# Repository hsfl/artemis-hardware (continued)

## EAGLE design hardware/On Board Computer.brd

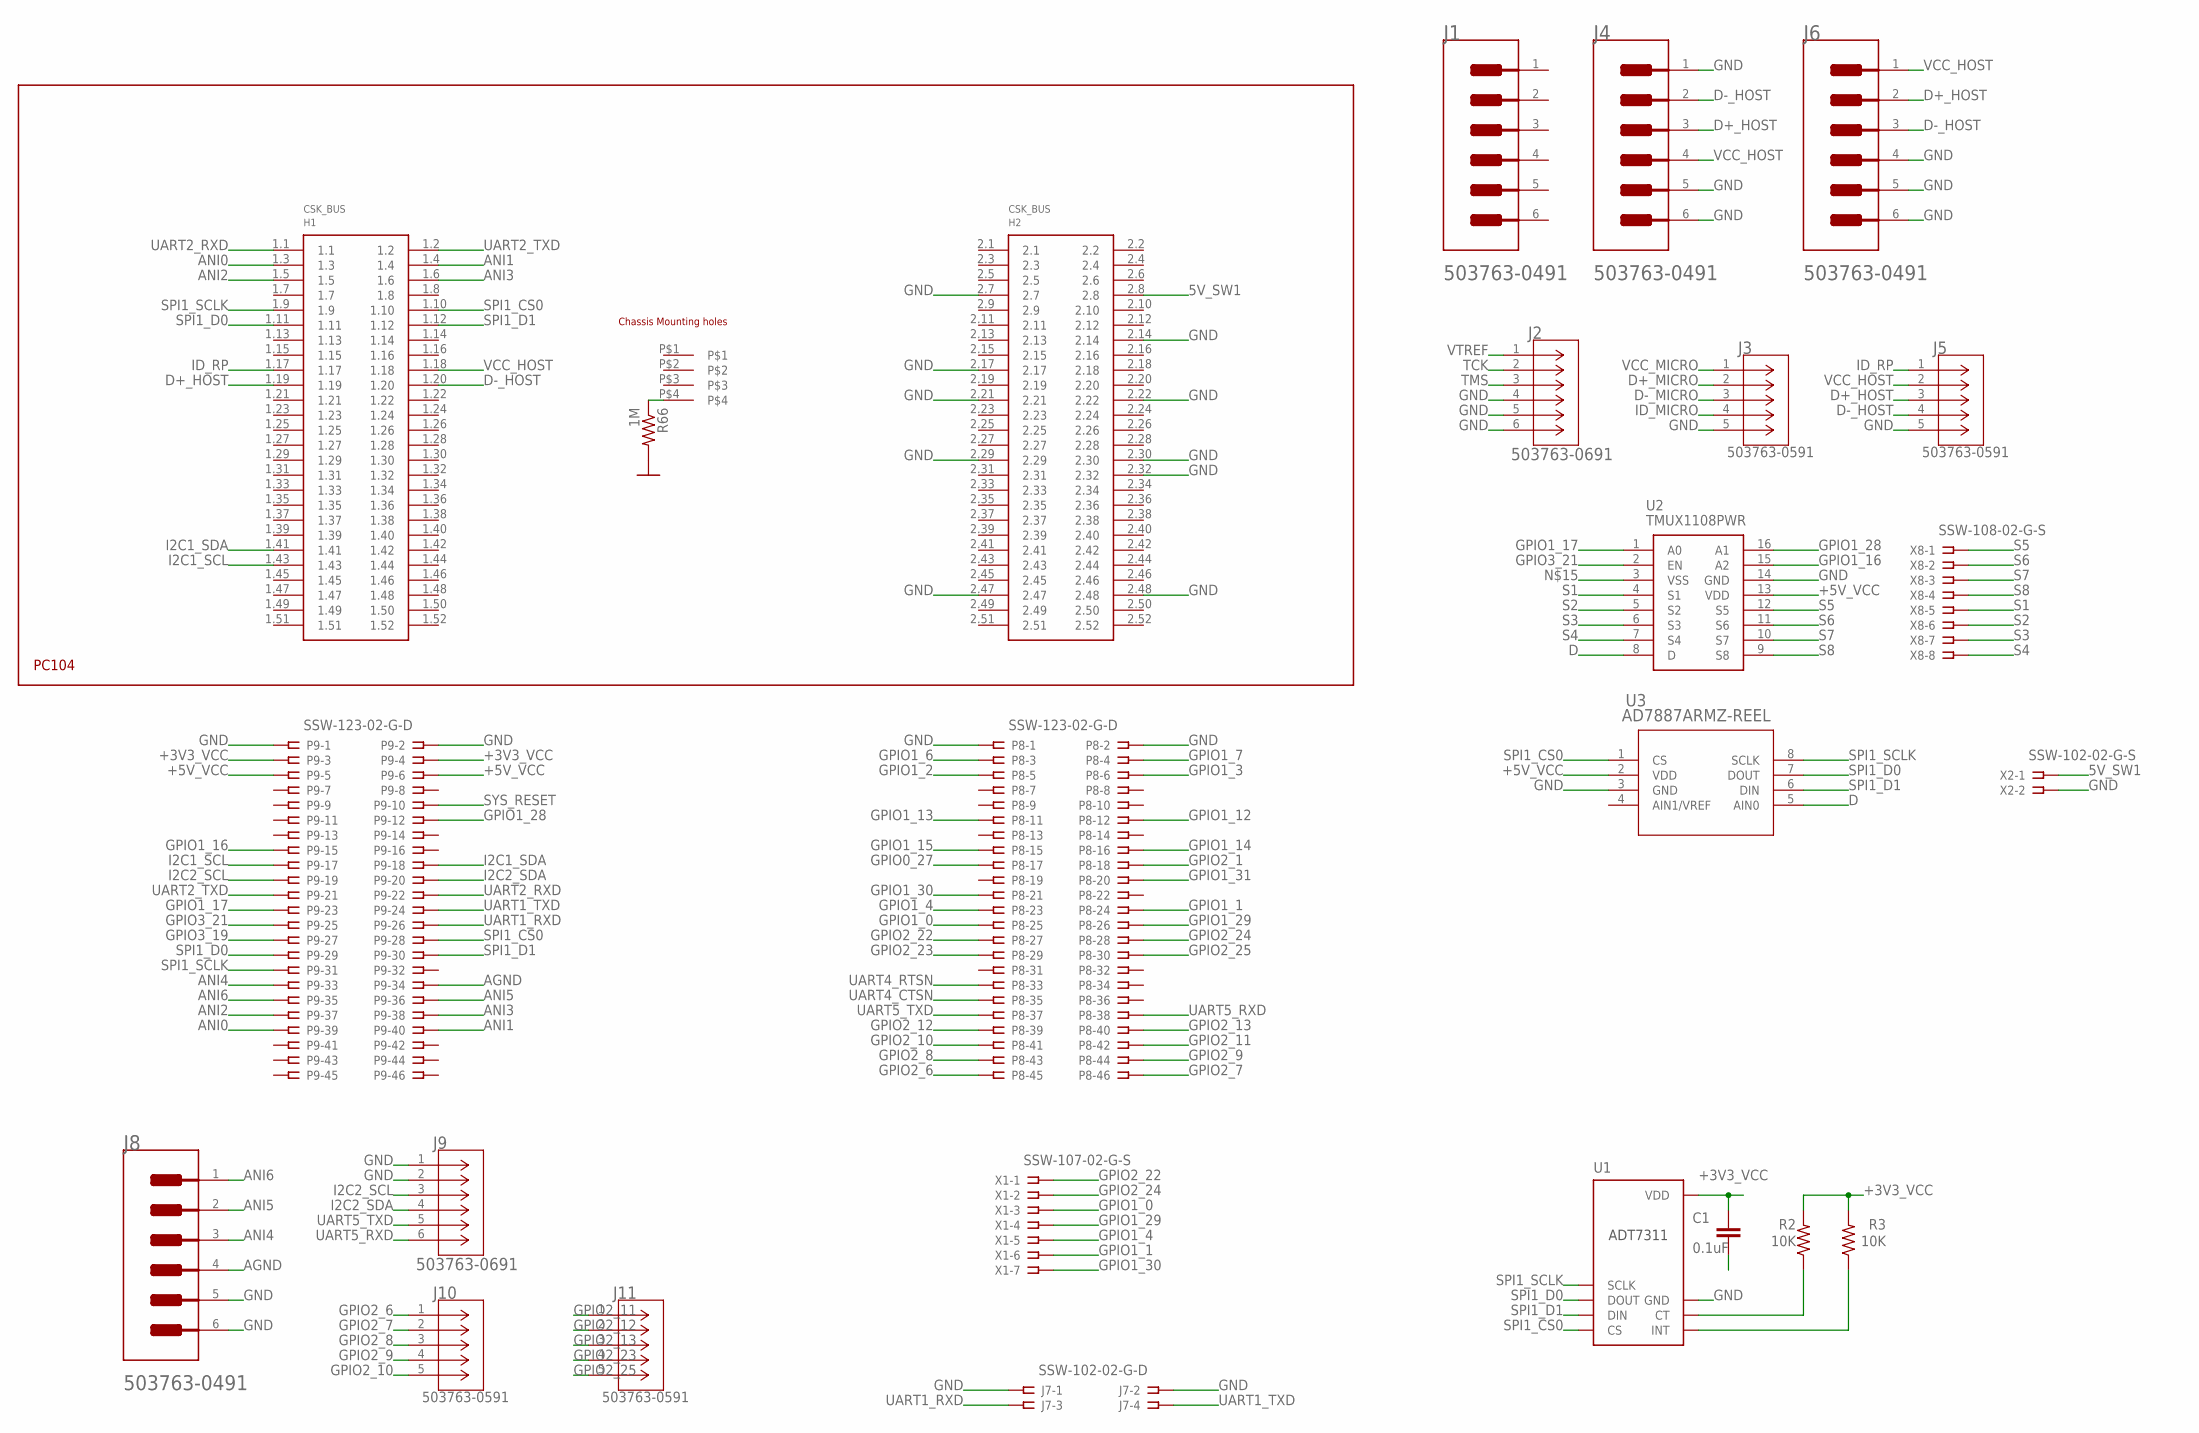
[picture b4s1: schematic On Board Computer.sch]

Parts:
C1: 0.1uF; 0805
H1: PC104_WCONN
J1, J4, J6, J8: MOLEX_503763-0491MOLEX_503763-0491_0_0; MOLEX_503763-0491_0
J2, J9: 503763-0691; CONN_503763-0691_MOL
J3, J5, J10, J11: 503763-0591; CONN_5037630591_MOL
J7: SSW-102-02-G-D
P8, P9: SSW-123-02-G-D
R2, R3: 10K; 0805
R66: 1M; 0805
U1: ADT7311; SOIC-8
U2: TMUX1108PWR; SOP65P640X120-16N
U3: AD7887ARMZ-REEL; RM_8_ADI
X1: SSW-107-02-G-S
X2: SSW-102-02-G-S
X8: SSW-108-02-G-S

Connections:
5V_SW1: H1.2.8, X2.1
+3V3_VCC: C1.1, P9.3, P9.4, R2.2, R3.2, U1.8 (VDD)
+5V_VCC: P9.5, P9.6, U2.13 (VDD), U3.2 (VDD)
AGND: J8.4, P9.34
ANI0: H1.1.3, P9.39
ANI1: H1.1.4, P9.40
ANI2: H1.1.5, P9.37
ANI3: H1.1.6, P9.38
ANI4: J8.3, P9.33
ANI5: J8.2, P9.36
ANI6: J8.1, P9.35
D: U2.8 (D), U3.5 (AIN0)
D+_HOST: H1.1.19, J4.3, J5.3, J6.2
D+_MICRO: J3.2
D-_HOST: H1.1.20, J4.2, J5.4, J6.3
D-_MICRO: J3.3
GND: C1.2, H1.2.7, H1.2.14, H1.2.17, H1.2.21, H1.2.22, H1.2.29, H1.2.30, H1.2.32, H1.2.47, H1.2.48, J2.4, J2.5, J2.6, J3.5, J4.1, J4.5 (MNT_1), J4.6 (MNT_2), J5.5, J6.4, J6.5 (MNT_1), J6.6 (MNT_2), J7.1, J7.2, J8.5 (MNT_1), J8.6 (MNT_2), J9.1, J9.2, P8.1, P8.2, P9.1, P9.2, R66.2, U1.7 (GND), U2.14 (GND), U3.3 (GND), X2.2
GPIO0_27: P8.17
GPIO1_0: P8.25, X1.3
GPIO1_1: P8.24, X1.6
GPIO1_2: P8.5
GPIO1_3: P8.6
GPIO1_4: P8.23, X1.5
GPIO1_6: P8.3
GPIO1_7: P8.4
GPIO1_12: P8.12
GPIO1_13: P8.11
GPIO1_14: P8.16
GPIO1_15: P8.15
GPIO1_16: P9.15, U2.15 (A2)
GPIO1_17: P9.23, U2.1 (A0)
GPIO1_28: P9.12, U2.16 (A1)
GPIO1_29: P8.26, X1.4
GPIO1_30: P8.21, X1.7
GPIO1_31: P8.20
GPIO2_1: P8.18
GPIO2_6: J10.1, P8.45
GPIO2_7: J10.2, P8.46
GPIO2_8: J10.3, P8.43
GPIO2_9: J10.4, P8.44
GPIO2_10: J10.5, P8.41
GPIO2_11: J11.1, P8.42
GPIO2_12: J11.2, P8.39
GPIO2_13: J11.3, P8.40
GPIO2_22: P8.27, X1.1
GPIO2_23: J11.4, P8.29
GPIO2_24: P8.28, X1.2
GPIO2_25: J11.5, P8.30
GPIO3_19: P9.27
GPIO3_21: P9.25, U2.2 (EN)
I2C1_SCL: H1.1.43, P9.17
I2C1_SDA: H1.1.41, P9.18
I2C2_SCL: J9.3, P9.19
I2C2_SDA: J9.4, P9.20
ID_MICRO: J3.4
ID_RP: H1.1.17, J5.1
unnamed: H1.P$4, R66.1
S1: U2.4 (S1), X8.5
S2: U2.5 (S2), X8.6
S3: U2.6 (S3), X8.7
S4: U2.7 (S4), X8.8
S5: U2.12 (S5), X8.1
S6: U2.11 (S6), X8.2
S7: U2.10 (S7), X8.3
S8: U2.9 (S8), X8.4
SPI1_CS0: H1.1.10, P9.28, U1.4 (CS), U3.1 (CS)
SPI1_D0: H1.1.11, P9.29, U1.2 (DOUT), U3.7 (DOUT)
SPI1_D1: H1.1.12, P9.30, U1.3 (DIN), U3.6 (DIN)
SPI1_SCLK: H1.1.9, P9.31, U1.1 (SCLK), U3.8 (SCLK)
SYS_RESET: P9.10
TCK: J2.2
TMS: J2.3
U11_CT: R2.1, U1.6 (CT)
U11_INT: R3.1, U1.5 (INT)
UART1_RXD: J7.3, P9.26
UART1_TXD: J7.4, P9.24
UART2_RXD: H1.1.1, P9.22
UART2_TXD: H1.1.2, P9.21
UART4_CTSN: P8.35
UART4_RTSN: P8.33
UART5_RXD: J9.6, P8.38
UART5_TXD: J9.5, P8.37
VCC_HOST: H1.1.18, J4.4, J5.2, J6.1
VCC_MICRO: J3.1
VTREF: J2.1

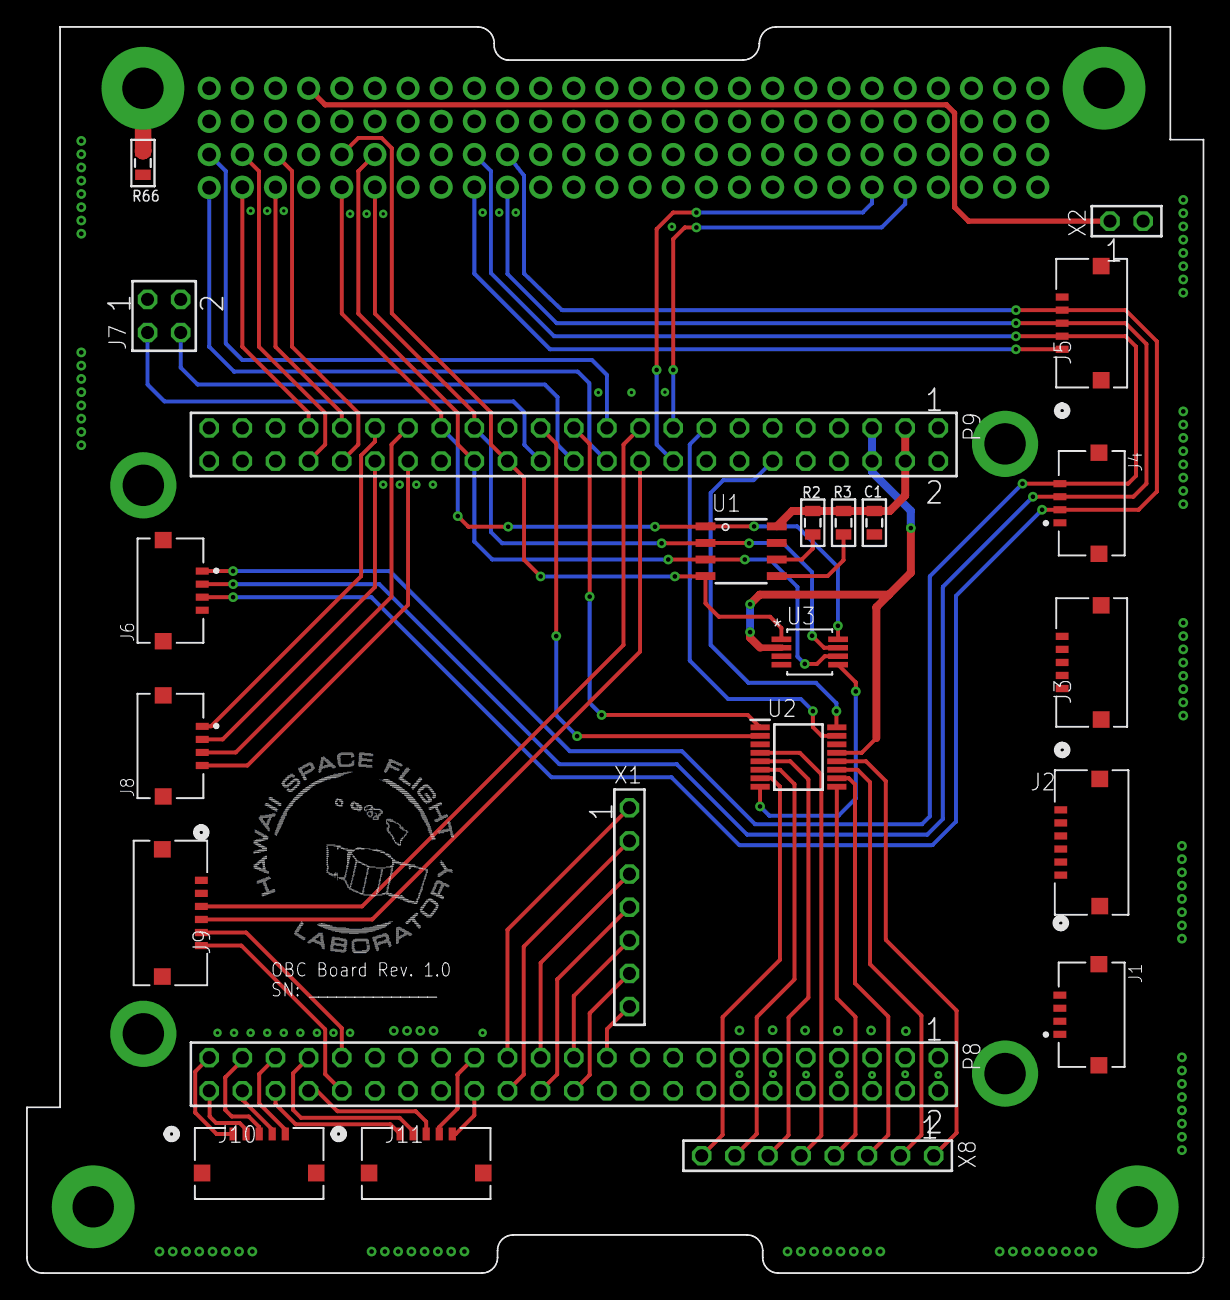
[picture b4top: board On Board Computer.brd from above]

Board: 2 copper layers, 90.2 x 95.5 mm, 24 parts (0 on the bottom side), 63 nets.
